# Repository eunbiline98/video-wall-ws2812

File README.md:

## Video Wall Led Strip WS2812 / WS2811

I am making a flexible LED display system using Processing to generate and transmit imagery via OSC

In Processing, I am generating animations, and then “downsampling” each frame to match the resolution of the NeoPixels by dividing the Processing frames into a array of square cells, finding the average color in each cell, and transmitting each row of cells to a specific ESP-32 as an OSC message.

# Hardware 
- Esp32 
- led strip ws2812 / ws2811
- PSU 5v (ws2812) / 12v (ws2812)
- Router

# Software
- Arduino IDE
- Processing IDE

# Documentation

Video
🡻🡻🡻🡻🡻

# Notes!!!

This is still a development process there are some problematic aspects could be due to messy data transfer from computer to esp32 via udp, or in terms of array , it is still unknown.

Please if you want to develop from my project, I'm very happy

Best Regards

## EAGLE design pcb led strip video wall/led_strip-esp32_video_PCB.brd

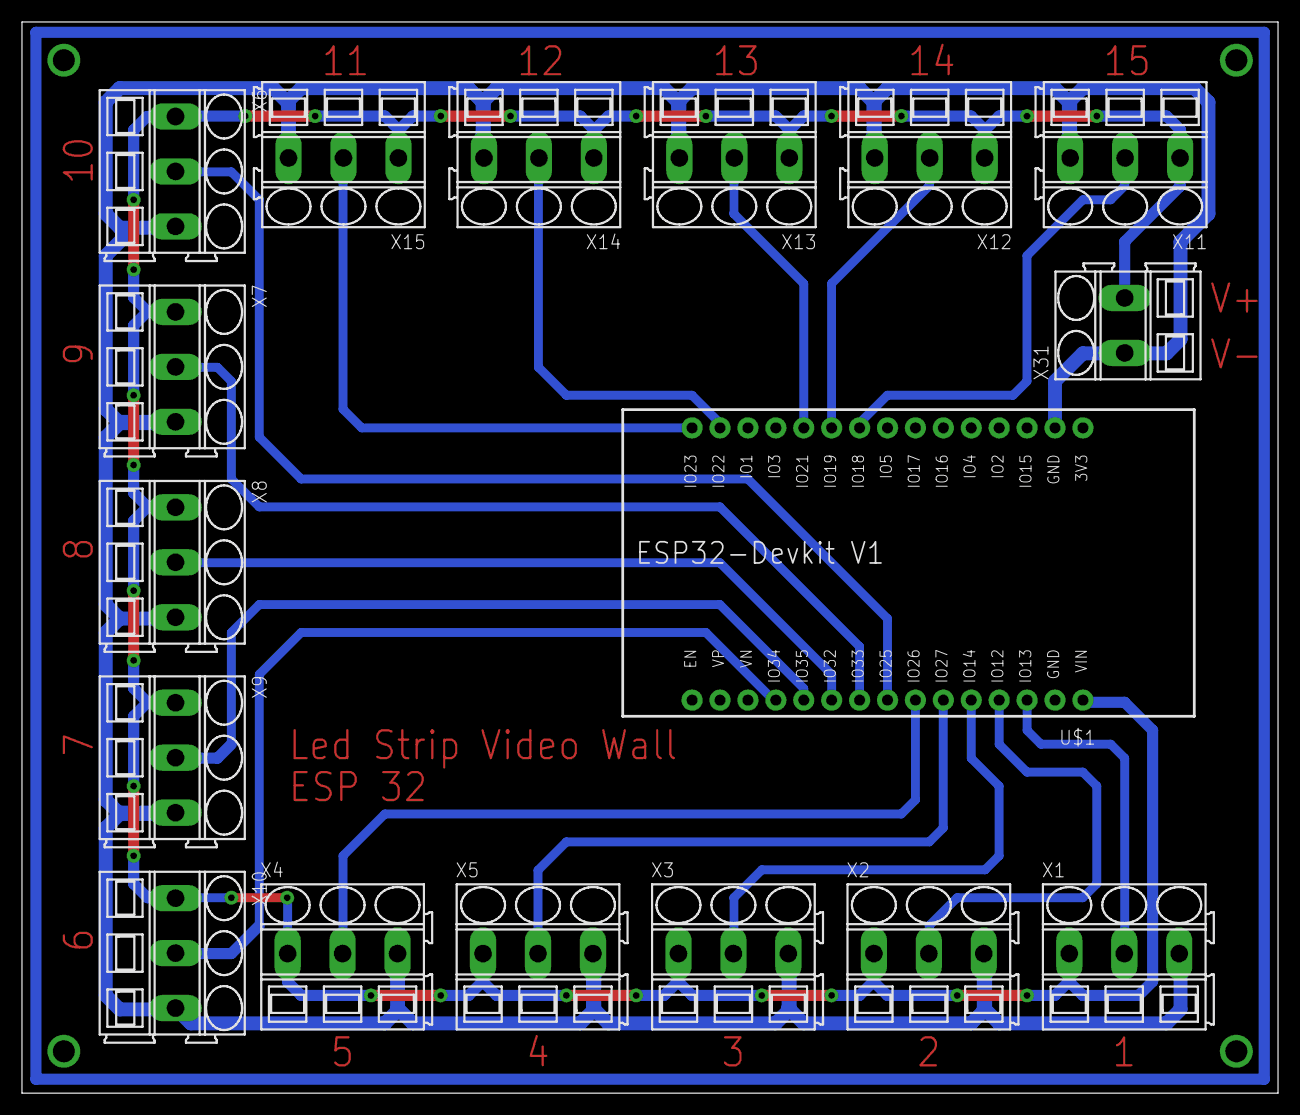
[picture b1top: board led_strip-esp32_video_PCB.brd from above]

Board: 2 copper layers, 114.3 x 97.5 mm, 17 parts (0 on the bottom side), 17 nets.

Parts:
U$1: ESP32DEVKITV1; ESP32-DEVKITV1
X1, X2, X3, X4, X5, X6, X7, X8, X9, X10, X11, X12, X13, X14, X15: SMKDSP_1,5/3
X31: SMKDSP_1,5/2

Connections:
+5V: U$1.30, X1.1, X2.1, X3.1, X4.1, X5.1, X6.1, X7.1, X8.1, X9.1, X10.1, X11.1, X12.1, X13.1, X14.1, X15.1, X31.2
GND: U$1.2, X1.3, X2.3, X3.3, X4.3, X5.3, X6.3, X7.3, X8.3, X9.3, X10.3, X11.3, X12.3, X13.3, X14.3, X15.3, X31.1
STRIP-1: U$1.28, X1.2
STRIP-2: U$1.27, X2.2
STRIP-3: U$1.26, X3.2
STRIP-4: U$1.24, X4.2
STRIP-5: U$1.24, X5.2
STRIP-6: U$1.23, X6.2
STRIP-7: U$1.22, X7.2
STRIP-8: U$1.21, X8.2
STRIP-9: U$1.20, X9.2
STRIP-10: U$1.19, X10.2
STRIP-11: U$1.9, X11.2
STRIP-12: U$1.10, X12.2
STRIP-13: U$1.11, X13.2
STRIP-14: U$1.14, X14.2
STRIP-15: U$1.15, X15.2

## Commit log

2021-07-15 Upload Program esp-32
2021-07-15 Upload Processing Code
2021-07-15 Board PCB Design
